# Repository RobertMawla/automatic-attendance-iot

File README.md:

# Automatic Attendance IoT — ESP32 + Fingerprint R558-S

## Wiring

### 1. ESP32 DevKit V1 dan R558-S

| Komponen | Pin komponen | ESP32 DevKit V1 | Keterangan |
|---|---|---|---|
| R558-S | TX | GPIO32 | UART RX ESP32 |
| R558-S | RX | GPIO33 | UART TX ESP32 |
| R558-S | TOUCH_OUT | GPIO34 | Opsional, untuk pemantauan sentuhan |
| R558-S | VCC_3.3V | 3.3V | Periksa pinout modul |
| R558-S | VCC_MCU | 3.3V | Ikuti datasheet varian yang digunakan |
| R558-S | GND | GND | Ground bersama |

Baud rate sensor fingerprint: **57600**.

### 2. MicroSD Module

| Pin MicroSD | ESP32 DevKit V1 | Keterangan |
|---|---|---|
| SCK / CLK | GPIO18 | SPI clock |
| MISO / DO | GPIO19 | SPI data keluar dari MicroSD |
| MOSI / DI | GPIO23 | SPI data masuk ke MicroSD |
| CS | GPIO13 | Chip select |
| VCC | 5V | Sesuai modul MicroSD yang digunakan |
| GND | GND | Ground bersama |

Pastikan modul MicroSD mendukung suplai 5V pada pin VCC. Tegangan logika keluarannya harus sesuai dengan batas aman GPIO ESP32, yaitu 3,3V.

### 3. RTC DS1307

| Pin RTC | ESP32 DevKit V1 | Keterangan |
|---|---|---|
| SDA | GPIO21 melalui level shifter yang sesuai | Jalur I2C |
| SCL | GPIO22 melalui level shifter yang sesuai | Jalur I2C |
| VCC | 5V | Sesuai modul DS1307 |
| GND | GND | Ground bersama |

**Penting:** DS1307 umumnya menggunakan pull-up I2C ke tegangan 5V. Jangan menghubungkan SDA dan SCL langsung ke ESP32 apabila jalurnya ditarik ke 5V. Gunakan level shifter dua arah yang sesuai.

### 4. MAX98357A dan Speaker

| Pin MAX98357A | ESP32 DevKit V1 / Komponen | Keterangan |
|---|---|---|
| DIN | GPIO27 | I2S data |
| BCLK | GPIO26 | I2S bit clock |
| LRC / LRCLK | GPIO25 | I2S word select |
| VDD | 5V | Suplai amplifier |
| GND | GND | Ground bersama |
| OUT+ | Speaker + | Output audio |
| OUT- | Speaker - | Output audio |

Kedua terminal speaker harus terhubung ke OUT+ dan OUT-. **Jangan menghubungkan OUT+ atau OUT- ke GND**, karena output amplifier merupakan tipe bridge.

### 5. LED RGB Common Cathode

Gunakan resistor **330 Ω secara seri pada setiap kanal LED**.

| Pin LED RGB | ESP32 DevKit V1 | Keterangan |
|---|---|---|
| R | GPIO2 melalui resistor 330 Ω | Kanal merah |
| G | GPIO15 melalui resistor 330 Ω | Kanal hijau |
| B | GPIO4 melalui resistor 330 Ω | Kanal biru |
| Common cathode | GND | Katoda bersama |

Pinout ini berlaku untuk LED RGB tipe common cathode.

### 6. Tombol Konfigurasi Wi-Fi

| Koneksi | ESP32 DevKit V1 | Keterangan |
|---|---|---|
| Kaki pertama tombol | GPIO14 | Input tombol |
| Kaki kedua tombol | GND | Ground |

Program menggunakan `INPUT_PULLUP`. Tombol akan terbaca LOW ketika ditekan.

- Tahan tombol selama 3 detik untuk meminta aktivasi mode konfigurasi.
- Tahan kembali selama 3 detik untuk meminta keluar dari mode konfigurasi.

Aktivasi Wi-Fi harus diverifikasi melalui Serial Monitor. Jika ESP32 mengalami reset ketika Wi-Fi diaktifkan, periksa log sebelum menggunakan fitur web.

### 7. Ground dan Suplai Daya

- Semua modul yang terhubung ke ESP32 harus memiliki referensi GND bersama.
- Gunakan suplai yang sesuai dengan kebutuhan tegangan dan arus masing-masing modul.
- Jangan menghubungkan dua sumber tegangan ke jalur yang sama tanpa memastikan rangkaiannya memang mendukung konfigurasi tersebut.
- Pastikan level logika seluruh sinyal yang masuk ke GPIO ESP32 tidak melebihi 3,3V.
- Jika menggunakan USB komputer untuk ESP32 dan adaptor eksternal untuk modul lain, pastikan GND kedua sistem terhubung bersama.
- Jangan menganggap suplai daya pasti cukup hanya berdasarkan nilai arus pada label adaptor; kestabilan tegangan saat beban berubah juga perlu diperhatikan.

## Pengaturan Arduino IDE

1. Instal paket board **esp32 by Espressif Systems** melalui Boards Manager.
2. Pilih board **ESP32 Dev Module**.
3. Pilih port COM ESP32 yang benar.
4. Instal library berikut melalui Library Manager:
   - **Adafruit Fingerprint Sensor Library** oleh Adafruit.
   - **RTClib** oleh Adafruit.
5. Buka sketch `Absensi_R558S_ESP32.ino`.
6. Unggah program dan buka Serial Monitor pada **115200 baud**.

Library Wi-Fi, WebServer, SPI, SD, Wire, dan I2S berasal dari paket board ESP32 atau framework yang digunakan sketch.

## Web Lokal

Jika mode Access Point berhasil diaktifkan:

1. Sambungkan laptop atau ponsel ke jaringan `Absensi-ESP32`.
2. Password awal: `absensi123`.
3. Buka `http://192.168.4.1`.
4. Gunakan formulir web untuk mendaftarkan pengguna dan mengatur waktu RTC.

Alamat, SSID, dan password harus sesuai dengan konfigurasi pada sketch yang digunakan.

## Isi MicroSD

Sketch menggunakan file berikut:

- `users.csv` — pemetaan ID fingerprint dan nama pengguna.
- `attendance.csv` — catatan tanggal, waktu, ID, nama, dan confidence.

Jangan mengubah ID pada `users.csv` tanpa menyesuaikan template fingerprint yang tersimpan di sensor.

## Audio MAX98357A

Salin file WAV ke direktori root MicroSD:

- `/sukses.wav` — audio ketika sidik jari cocok.
- `/coba_lagi.wav` — audio ketika sidik jari tidak dikenal atau pendaftaran gagal.
- `/terima_kasih.wav` — audio setelah pendaftaran berhasil.

Format yang didukung sesuai implementasi sketch: **WAV PCM 16-bit**, mono atau stereo, dengan sample rate 8.000–48.000 Hz. Mengganti ekstensi MP3 menjadi WAV tidak mengubah format audio.

## Catatan Penggunaan

- GPIO34 merupakan input-only dan tidak memiliki internal pull-up/pull-down. Pastikan sinyal TOUCH_OUT sesuai dengan level logika ESP32.
- Pemindaian fingerprint dilakukan melalui komunikasi UART dengan sensor, bukan semata-mata berdasarkan sinyal TOUCH_OUT.
- Anti-log duplikat menggunakan jeda 30 detik untuk ID yang sama; ini bukan aturan satu kali per hari.
- Jika RTC tidak tersedia, catatan dapat menggunakan penanda `RTC_UNAVAILABLE`, sesuai implementasi sketch.
- Ganti password Wi-Fi contoh sebelum sistem digunakan.
- Fitur penghapusan pengguna melalui web, ekspor CSV melalui web, autentikasi admin tambahan, dan sinkronisasi server belum tersedia dalam versi ini.

## Troubleshooting Wi-Fi

Jika ESP32 berjalan normal tanpa Wi-Fi tetapi reset saat `WiFi.mode(WIFI_AP)` dipanggil:

1. Uji sketch Wi-Fi minimal tanpa perangkat eksternal.
2. Bandingkan hasilnya menggunakan board ESP32 lain dengan sketch dan konfigurasi yang sama.
3. Catat log Serial Monitor lengkap sebelum

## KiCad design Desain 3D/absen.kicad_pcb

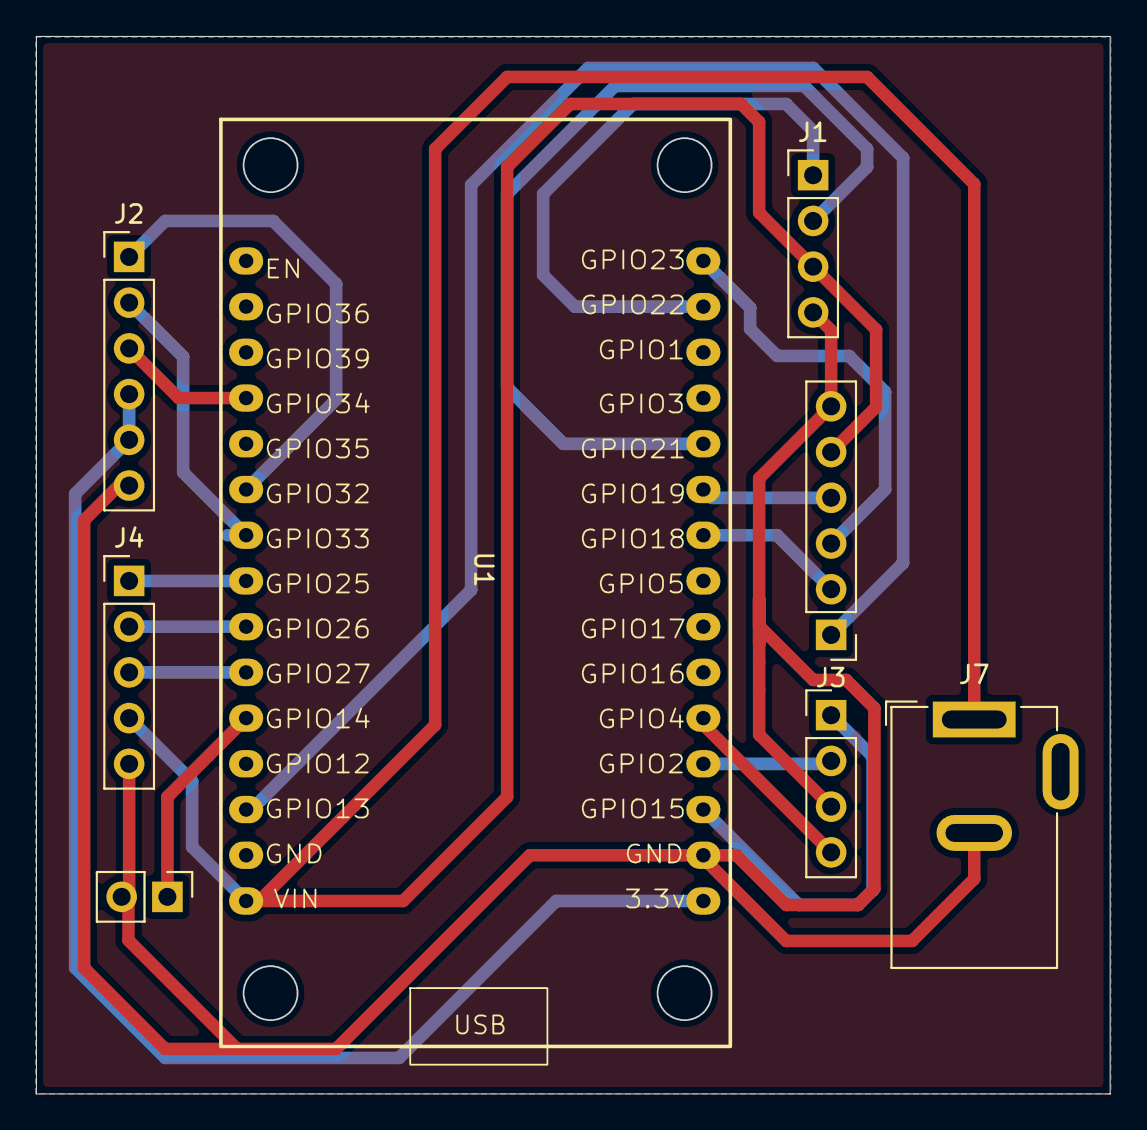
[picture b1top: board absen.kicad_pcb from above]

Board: 2 copper layers, 59.7 x 58.8 mm, 8 parts (0 on the bottom side), 19 nets.

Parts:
J: LED; PinHeader_1x04_P2.54mm_Vertical
J1: RTC; PinHeader_1x04_P2.54mm_Vertical
J2: R558; PinHeader_1x06_P2.54mm_Vertical
J3: Micro SD; PinHeader_1x06_P2.54mm_Vertical
J4: MAX; PinHeader_1x05_P2.54mm_Vertical
J6: Button; PinHeader_1x02_P2.54mm_Vertical
J7: Barrel_Jack_Switch; BarrelJack_GCT_DCJ200-10-A_Horizontal
U1: ESP32_30pin

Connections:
unnamed: J1.1, U1.29 (GPIO22)
unnamed: J1.2, U1.26 (GPIO21)
unnamed: J1.3, J3.5, J4.4, J7.1, U1.1 (VIN)
unnamed: J.3, J1.4, J2.6, J3.6, J4.5, J6.2, J7.2, U1.17 (GND)
unnamed: J2.1, U1.10 (GPIO32)
unnamed: J2.2, U1.9 (GPIO33)
unnamed: J2.3, U1.12 (GPIO34)
unnamed: J2.4, J2.5, U1.16 (3.3v)
unnamed: J3.1, U1.3 (GPIO13)
unnamed: J3.2, U1.24 (GPIO18)
unnamed: J3.3, U1.30 (GPIO23)
unnamed: J3.4, U1.25 (GPIO19)
unnamed: J4.1, U1.8 (GPIO25)
unnamed: J4.2, U1.7 (GPIO26)
unnamed: J4.3, U1.6 (GPIO27)
unnamed: J.1, U1.18 (GPIO15)
unnamed: J.2, U1.19 (GPIO2)
unnamed: J.4, U1.20 (GPIO4)
unnamed: J6.1, U1.5 (GPIO14)
